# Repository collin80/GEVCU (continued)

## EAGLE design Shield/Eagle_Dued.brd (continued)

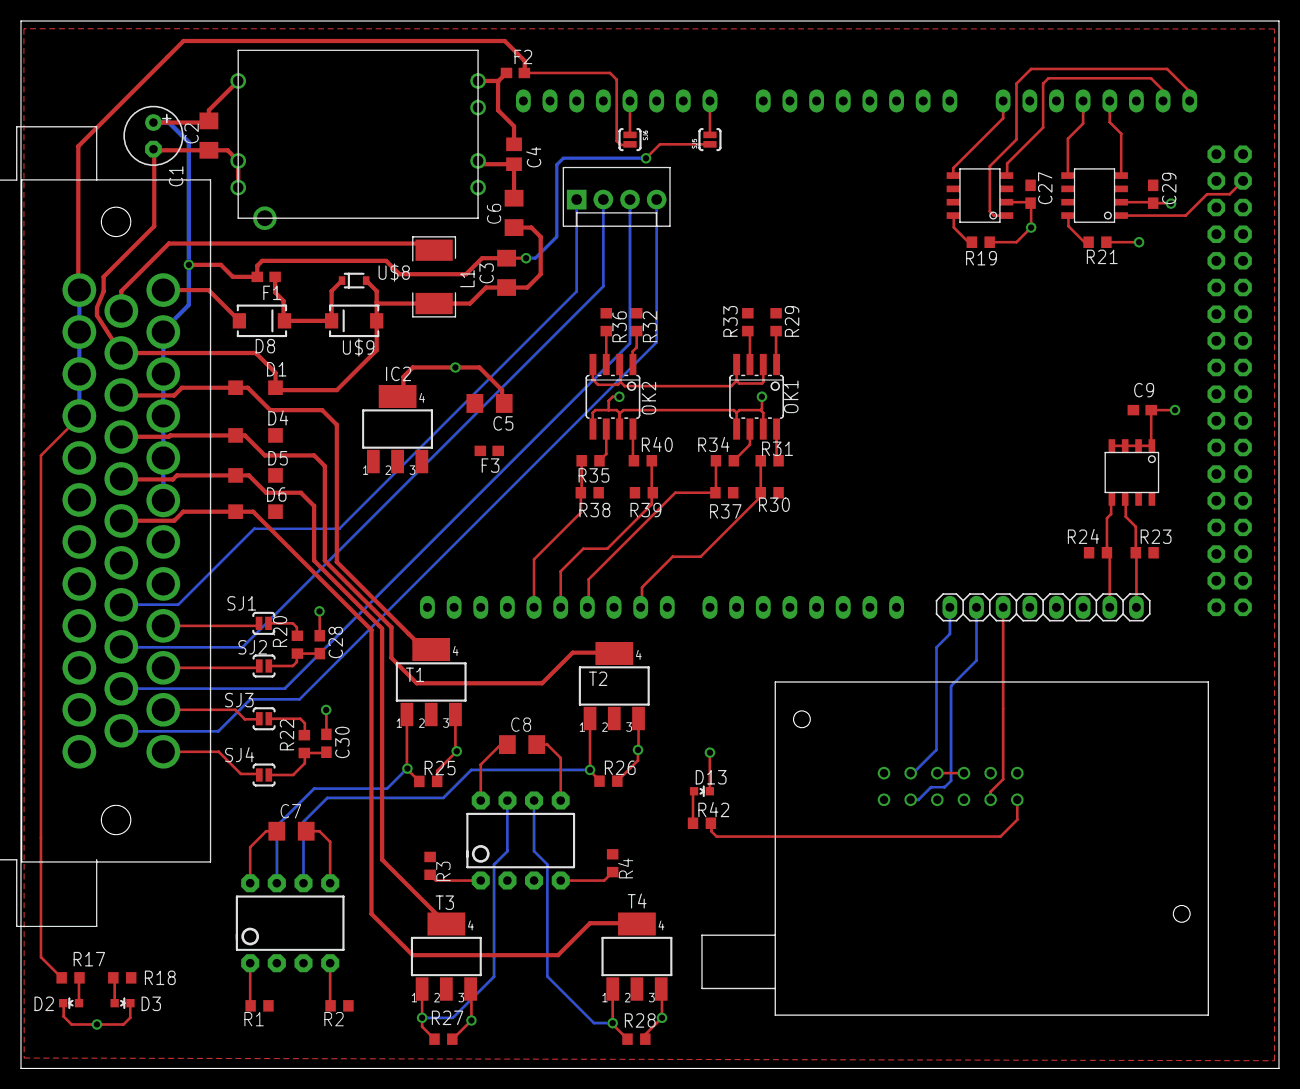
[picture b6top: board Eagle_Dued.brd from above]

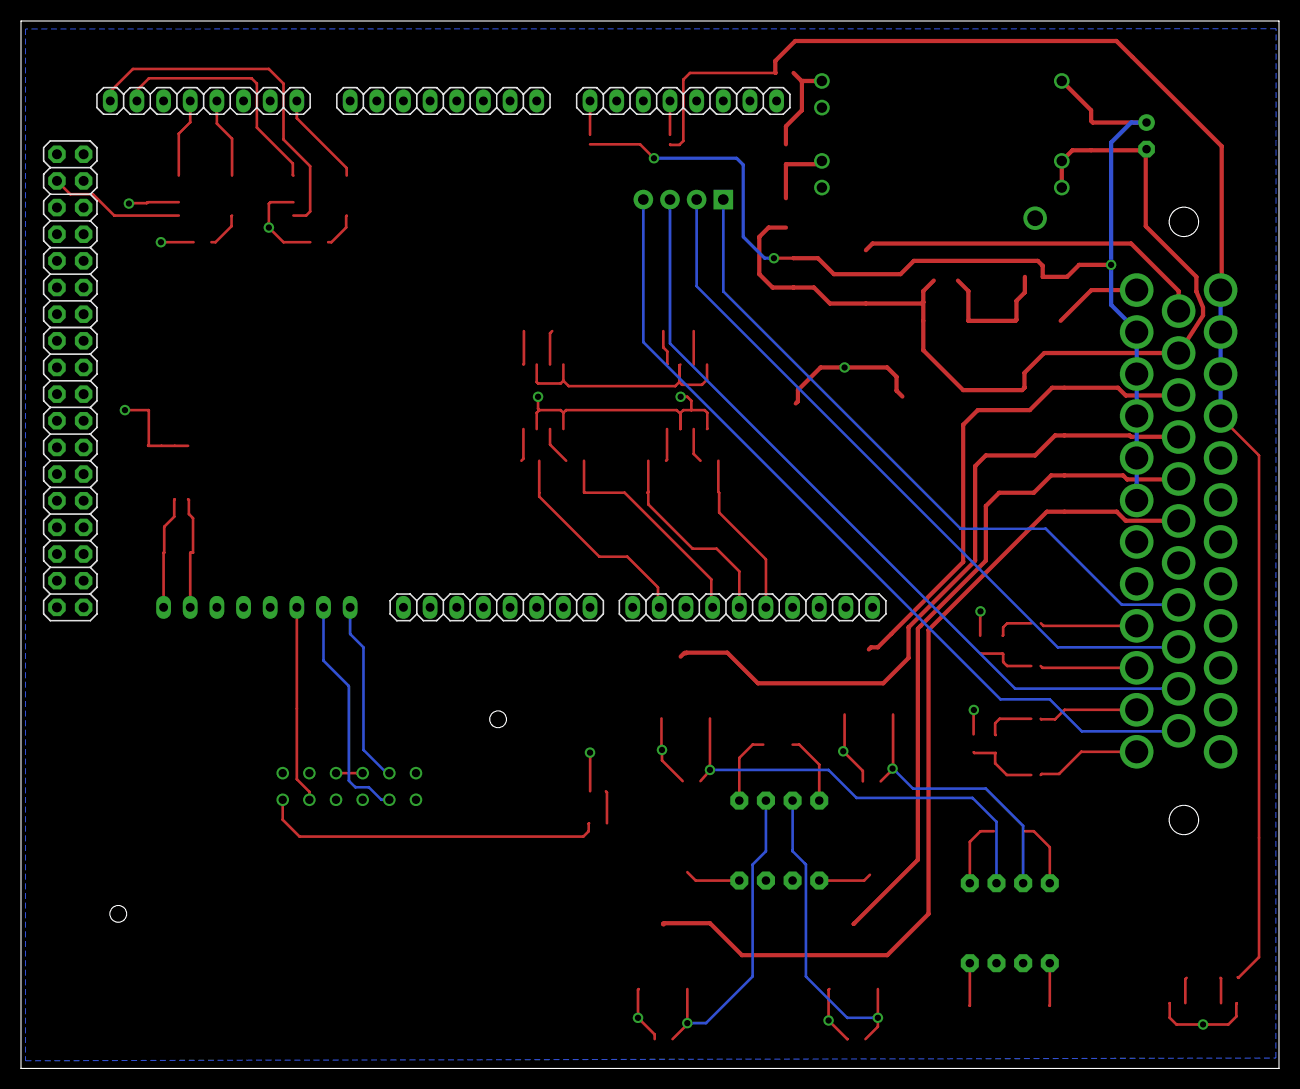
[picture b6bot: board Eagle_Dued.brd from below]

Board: 2 copper layers, 119.9 x 99.8 mm, 85 parts (6 on the bottom side), 76 nets.

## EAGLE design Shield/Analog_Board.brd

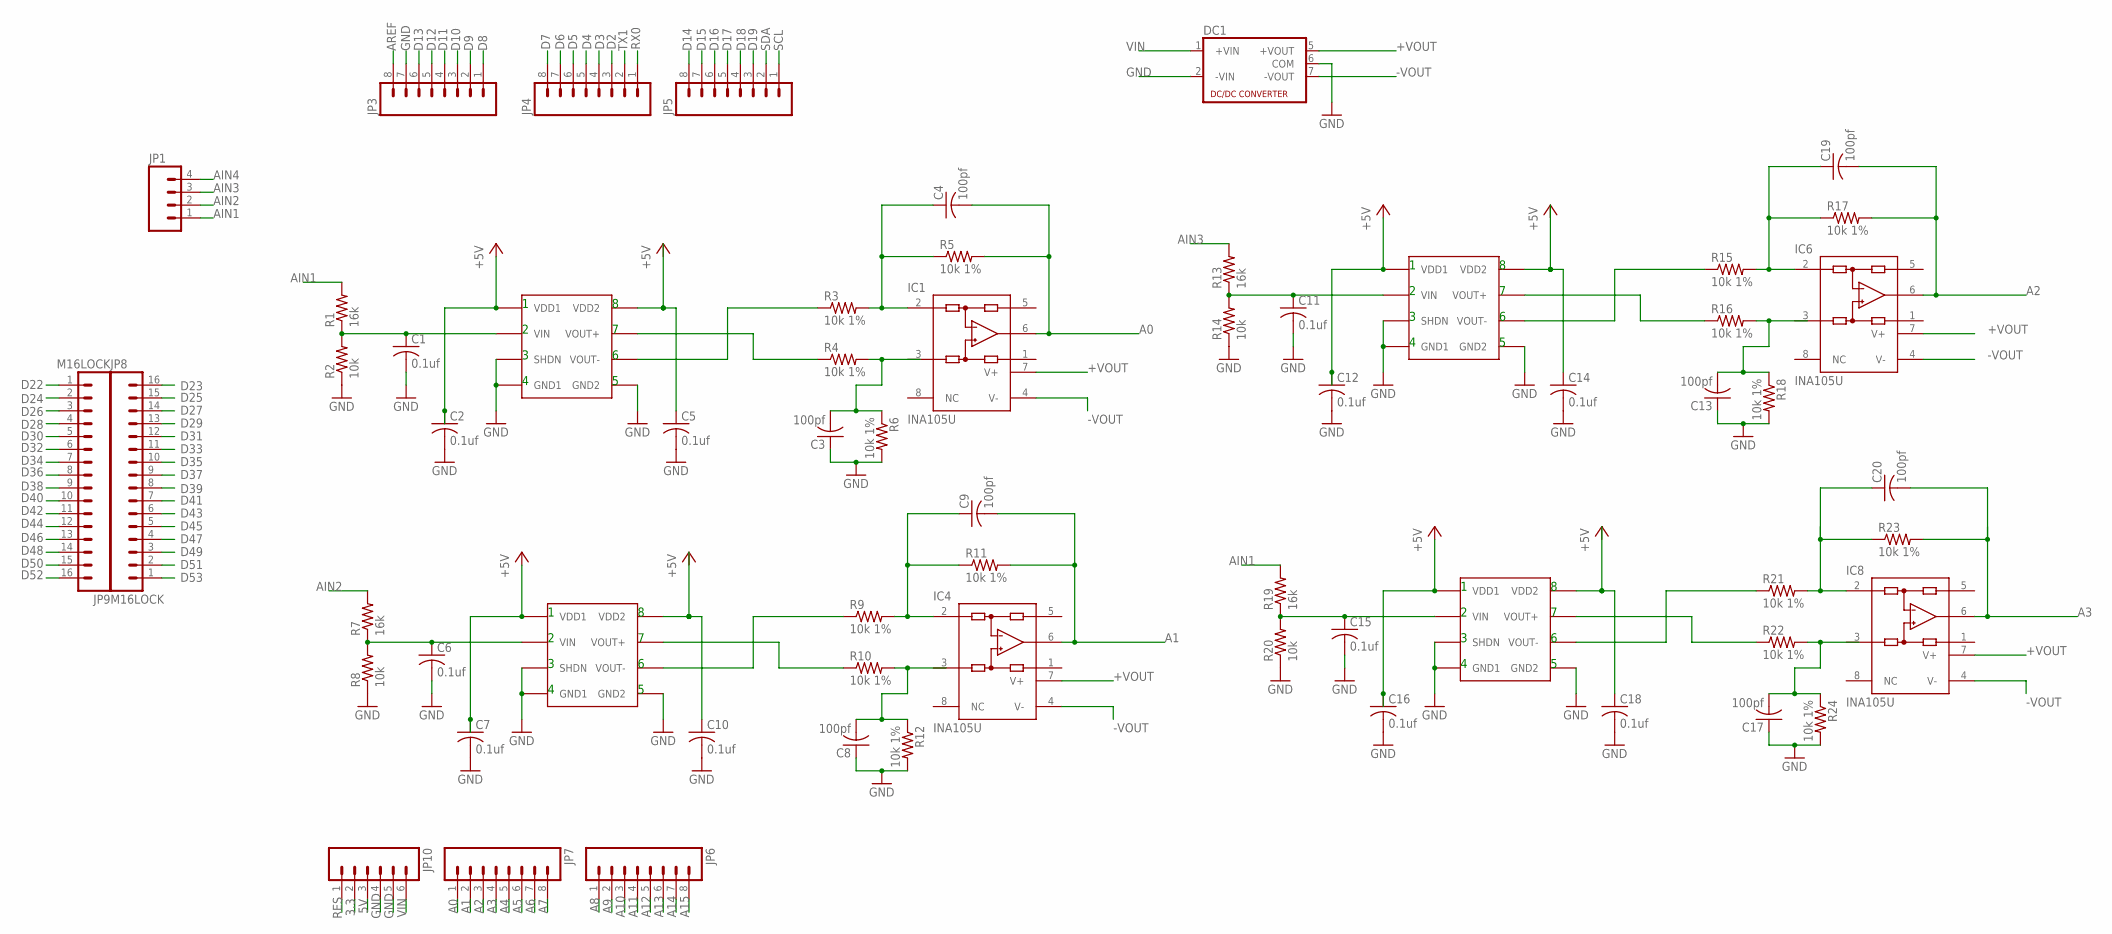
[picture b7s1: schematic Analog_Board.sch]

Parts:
C1, C2, C5, C6, C7, C10, C11, C12, C14, C15, C16, C18: 0.1uf; C0603
C3, C4, C8, C9, C13, C17, C19, C20: 100pf; C0603
DC1: NMASIP8; NMA
IC1, IC4, IC6, IC8: INA105U; SO08
IC2, IC3, IC5, IC7: ACPL-C87A-000E; SO8-WIDE
JP1: M04LOCK; 1X04_LOCK
JP3, JP4, JP5, JP6, JP7: M08LOCK; 1X08_LOCK
JP8, JP9: M16LOCK; 1X16_LOCK
JP10: M06LOCK; 1X06_LOCK
R1, R7, R13, R19: 16k; R0603
R2, R8, R14, R20: 10k; R0603
R3, R4, R5, R6, R9, R10, R11, R12, R15, R16, R17, R18, R21, R22, R23, R24: 10k 1%; R0603

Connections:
3.3: JP10.2
5V: JP10.3
+5V: C2.1, C5.1, C7.1, C10.1, C12.1, C14.1, C16.1, C18.1, IC2.1 (VDD1), IC2.8 (VDD2), IC3.1 (VDD1), IC3.8 (VDD2), IC5.1 (VDD1), IC5.8 (VDD2), IC7.1 (VDD1), IC7.8 (VDD2)
+VOUT: DC1.5 (+VOUT), IC1.7 (V+), IC4.7 (V+), IC6.7 (V+), IC8.7 (V+)
-VOUT: DC1.7 (-VOUT), IC1.4 (V-), IC4.4 (V-), IC6.4 (V-), IC8.4 (V-)
A0: C4.2, IC1.6 (OUT), JP7.1, R5.2
A1: C9.2, IC4.6 (OUT), JP7.2, R11.2
A2: C19.2, IC6.6 (OUT), JP7.3, R17.2
A3: C20.2, IC8.6 (OUT), JP7.4, R23.2
A4: JP7.5
A5: JP7.6
A6: JP7.7
A7: JP7.8
A8: JP6.1
A9: JP6.2
A10: JP6.3
A11: JP6.4
A12: JP6.5
A13: JP6.6
A14: JP6.7
A15: JP6.8
AIN2: JP1.2, R7.2
AIN3: JP1.3, R13.2
AREF: JP3.8
D2: JP4.3
D3: JP4.4
D4: JP4.5
D5: JP4.6
D6: JP4.7
D7: JP4.8
D8: JP3.1
D9: JP3.2
D10: JP3.3
D11: JP3.4
D12: JP3.5
D13: JP3.6
D14: JP5.8
D15: JP5.7
D16: JP5.6
D17: JP5.5
D18: JP5.4
D19: JP5.3
D22: JP9.1
D23: JP8.16
D24: JP9.2
D25: JP8.15
D26: JP9.3
D27: JP8.14
D28: JP9.4
D29: JP8.13
D30: JP9.5
D31: JP8.12
D32: JP9.6
D33: JP8.11
D34: JP9.7
D35: JP8.10
D36: JP9.8
D37: JP8.9
D38: JP9.9
D39: JP8.8
D40: JP9.10
D41: JP8.7
D42: JP9.11
D43: JP8.6
D44: JP9.12
D45: JP8.5
D46: JP9.13
D47: JP8.4
D48: JP9.14
D49: JP8.3
D50: JP9.15
D51: JP8.2
D52: JP9.16
D53: JP8.1
GND: C1.2, C2.2, C3.1, C5.2, C6.2, C7.2, C8.1, C10.2, C11.2, C12.2, C13.1, C14.2, C15.2, C16.2, C17.1, C18.2, DC1.2 (-VIN), DC1.6 (COM), IC2.3 (SHDN), IC2.4 (GND1), IC2.5 (GND2), IC3.3 (SHDN), IC3.4 (GND1), IC3.5 (GND2), IC5.3 (SHDN), IC5.4 (GND1), IC5.5 (GND2), IC7.3 (SHDN), IC7.4 (GND1), IC7.5 (GND2), JP3.7, JP10.4, JP10.5, R2.1, R6.2, R8.1, R12.2, R14.1, R18.2, R20.1, R24.2
unnamed: C20.1, IC8.2 (-IN), R21.2, R23.1
unnamed: IC2.7 (VOUT+), R4.1
unnamed: IC2.6 (VOUT-), R3.1
unnamed: C4.1, IC1.2 (-IN), R3.2, R5.1
unnamed: C1.1, IC2.2 (VIN), R1.1, R2.2
unnamed: C3.2, IC1.3 (+IN), R4.2, R6.1
unnamed: C6.1, IC3.2 (VIN), R7.1, R8.2
unnamed: IC3.7 (VOUT+), R10.1
unnamed: IC3.6 (VOUT-), R9.1
unnamed: C9.1, IC4.2 (-IN), R9.2, R11.1
unnamed: C8.2, IC4.3 (+IN), R10.2, R12.1
unnamed: C11.1, IC5.2 (VIN), R13.1, R14.2
unnamed: IC5.7 (VOUT+), R16.1
unnamed: IC5.6 (VOUT-), R15.1
unnamed: C19.1, IC6.2 (-IN), R15.2, R17.1
unnamed: C13.2, IC6.3 (+IN), R16.2, R18.1
unnamed: C15.1, IC7.2 (VIN), R19.1, R20.2
unnamed: IC7.7 (VOUT+), R22.1
unnamed: IC7.6 (VOUT-), R21.1
unnamed: C17.2, IC8.3 (+IN), R22.2, R24.1
RES: JP10.1
RX0: JP4.1
SCL: JP5.1
SDA: JP5.2
TX1: JP4.2
VIN: DC1.1 (+VIN), JP10.6

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
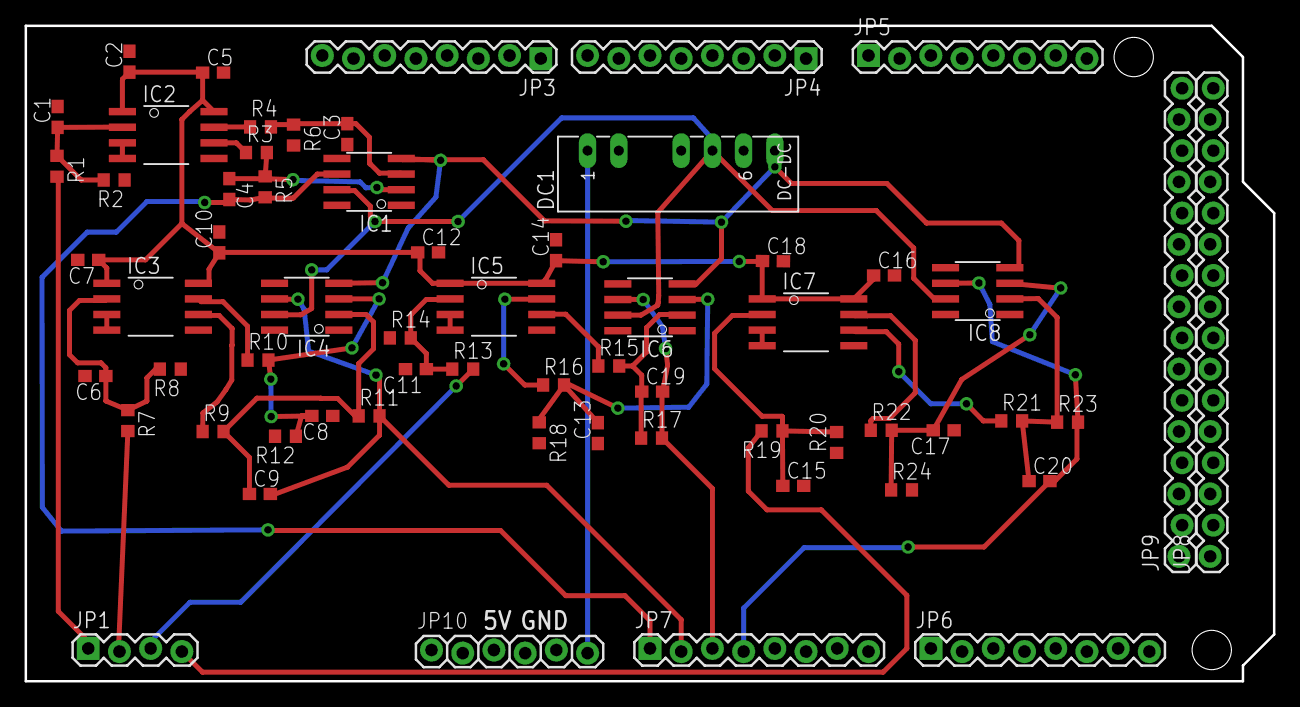
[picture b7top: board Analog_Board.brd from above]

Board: 2 copper layers, 101.6 x 53.3 mm, 62 parts (0 on the bottom side), 33 nets.

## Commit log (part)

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2014-08-21 Documentation
    Updated user manual. Added diagram for UQM Deutsche connector
2014-08-23 REVERSE and ENABLE functions
    Added annunciators for digital inputs 0-3 and the ENABLE and REVERSE
    annunciators.
2014-08-27 Added the ability to set motoring mode to either torque control or speed control. This should be exposed on the web interface as well. Also did some minor formatting.
2014-09-01 Double the ichip buffer size
2014-09-01 WiReach Setup moved to GEVCU.ino setup()
    That’s about it.
2014-09-02 Added CANCEL to loopcount
    Once Serial Console has forced ICHIP to load parameters, it sets a
    CANCEL bool to discontinue the count.
2014-09-05 Updated the readme. It was really out of date.
2014-09-07 Adjustments for Website Preload
2014-09-08 Fleshed out the FaultHandler some more. It now keeps a global log of uptime so that faults can be correlated to running time.
2014-09-16 UQM Changes and Temperature Changes
    Altered calculations for DMOC temperatures and UQM torque. Checked
    ENABLE and REVERSE inputs on UQM
2014-09-17 Changes to DMOC code to make it respect enable and reverse inputs.
2014-09-21 Postmerge
2014-09-22 Running Lights
    I’ve repurposed the RUNNING light on the STATUS panel and the running
    variable to indicate that we are receiving frames from the
    inverter/controller. If no frames are received for a certain time, the
    light goes out. If we never receive frames, it never comes on.
    In this way, we will know we are communicating or at least receiving
    traffic if we have a RUNNING advisory on the STATUS page.
2014-09-23 Tested on DMOC Bench and THING
    Reverse works. Enable works. Tested on DMOC bench and on VW Thing.
2014-09-28 Addition of the ability to set the ADC pins for pot based throttle and brake.
2014-10-02 Updated Web Site
2014-10-07 Incorporated Collin's NUKE command
2014-10-16 DC-DC COnverter Corrections
2014-10-17 Removed WIFI init
2014-12-11 Add common name to ThinkBatteryManager so it doesn't report itself as "Generic Device" any longer.
2014-12-17 Harmonize on using bool instead of boolean
    It's not good to mix bool and boolean in Arduino code for the Due. There are some subtle problems that can crop up. It's best to use the built-in C++ type "bool" when you want boolean values.
2014-12-19 Somewhat untested additions and modifications to ELM327 and OBDII stuff.
2014-12-23 Changes to make ichip code work more reliably and to aid in debugging. Also, fault handler was broken so it has been disabled for now.
2015-01-19 Add a driver class for the RX8 Dashboard. Uses the second canbus.
2015-02-25 Change BatteryManager so that it could be directly instantiated and isn't an abstract class any longer.
2015-02-25 Now using the new global objects in more places.
2015-03-01 Added a configuration object that is global and easy to use.
2015-03-06 Implementation of a new eeprom idea.
2015-03-18 move logging of 'add device' to device manager
2015-03-31 updated can matrix
2015-03-31 SystemIO sends status CAN msg and reads temperature
2015-04-09 move CanIO to separate device
2015-05-12 devices can be enabled/disabled without restart (via sendMessage()) adjust naming of output fields/variables devices can react on state change by implementing handleStateChange() devices power on the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
2015-05-12 refactor BrusaNLG5 and Charger: move general config+logic to super-class device is functional now, but NOT SAFE YET !! termination not implemented yet --> manual termination only
2015-05-14 include termination & security measures in charger, temperature derating/hysterese not implemented yet. Chargging should be quite safe now
2015-05-15 first compile, then commit...
2015-05-18 support controlling of cooling pump
2015-05-28 re-enable throttle ramping below regenMax
2015-06-09 fix conflict between eeprom and wifi, clean-up prefs handling, fix dashboard jumping needles
2015-06-12 MotorController refactoring move maxMechanicalPowerMotor, maxMechanicalPowerRegen to MotorControllerConfig as DMOC also supports it -> now configurable for DMOC handleStateChange now also passes the 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
2015-06-13 correctly handle REVERSE gear in conjunction with invertDirection
2015-06-14 fix ping assignment for GEVCU4.3 (regression from testing on v2)
2015-06-14 remove unnecessary reference to due_rtc
2015-08-13 Added CANio to canhandler
    Allow receipt of a CAN message to set digital outputs.
    Receipt of this message will trigger response of three messages to show
    state of digital outputs, analog inputs, and digital inputs.
2015-08-13 CANIO refactor
    Cleaned up CANIO a bit
2015-09-22 Initialize Wire in MemCache instead of setup()
2015-10-02 re-add PrefHandler in constructor of device subclass
    instantiate PrefHandler in constructor again as in super-class constructor getType() of sub-class can't be called
    simplify CAN data assignment in CanIO
    add analog data to CanIO messages
    move pin numbers to config.h
    add eeprom memory layout to comment of eeprom_layout.h
2015-10-14 error state was not broadcast correctly
2016-03-14 fix small bugs - if motor direction is inverted, show the value of rpm, throttle, etc. with correct sign - wifi wait longer to load params to prevent problems (no params loaded) - set hidden values f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
2016-03-25 fix typos
2016-03-26 updated website image with latest version
2016-03-28 set gauge ranges dynamically
2016-03-31 optimize WebSocket communication, recognize closure of socket by client fixed bugs
2016-04-07 fix typo
2016-04-08 remove slewType, we'll only support linear slew-rate
2016-04-17 increase update rate of ichip sockets
2016-05-24 change kwH variables to energy consumption the previous variable name was wrong and missleading also changed the calculation of used energy
2016-05-26 provide additional data from charger/dcdc to webSocktet
2016-06-04 fix wrong battery temp which caused the charger not to start fix missing 0 char at end of decoded incoming data from websocket
2016-06-06 fixed bug in slew calculation, caused jerky reduction in power correct: if(torqueTarget < torqueRequested), wrong: if(torqueTarget < 0) also apply slew for negative torque --> removed unnecessary cod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
2016-06-09 add new state "shutdown", fix WebSocket msg handling
2016-06-21 change logging so that messages can be pushed to WebSocket
2016-06-21 add warning and error sounds to dashboard
2016-06-27 add new info/warn/error sounds for notification clean-up web page
2016-06-29 clean-up a bit
2016-07-01 make start-up of charging more resilient against old error messages
2016-08-17 allow setting the energy consumption manually
2016-09-08 adjust torque/speed calculation, add support for ABS -> torque = 0
2016-09-16 print more error messages from devices to log
2016-09-17 fix wrong format descriptors in logger formatting
2016-09-22 Updated readme to cover a recent issue with this repo
2016-11-13 minor improvements
2016-11-25 keep the system running if motor controller reports error (the DCDC might still be needed), only disable the motor give the charger more time to recover from lost messages
2016-12-03 prevent continuous saving of charge state if 0 but DCDC increases it again a tiny bit
2016-12-04 optimize website
2016-12-08 fix no regen at low temperatures
2016-12-09 optimize gauge performance by using layers, prepare for multi-dial gauges
2016-12-17 finally fix start-up issues (?)
2016-12-19 config change
2016-12-26 add a 3 dial gauge for testing
2016-12-28 get gradients working for arcs
2016-12-29 more performance tweaks
2017-01-03 webservice and every dial now has its own worker (thread) which improves performance on slow multi-core systems (like the Pi or a tablet)
2017-01-04 automatically reset wifi if it does no longer respond enable/disable heater, ehps, creep, regen via websocket process heater info from GEVCUExtension
2017-01-05 first working edition of new dashboard overcame some quirks of ichip (website packager)
2017-01-08 overcome more quirks of ichip (some files can't be in sub-dir)
2017-01-10 adjust handling of heater temperature via CAN bus
2017-01-10 ensure that also 0 values are rendered
2017-02-01 fix websocket handling issues
2017-02-02 fix handling of floats reduce severity level of some log messages
2017-02-07 log incoming socket messages drop dead code
2017-03-11 prevent unnecessary writes to eeprom (prolongue live)
2017-03-11 init all values
2017-03-20 set correct pin for led on GEVCU4 board
2017-03-20 fix setting of ADC gain/offset on purged eeprom fix configuration if raw ADC should be used adjust calculation of fuel level
2017-03-23 move hardcoded values from config.h to devices align naming of defines in eeprom_layout.h move config of ADC offset/gain from eeprom to config.h
2017-03-26 make brake hold coefficient configurable find force at highest speed --> same force reuired to hold apply this force once the car stands still
2017-04-01 log ratio of motor/vehicle speed
2017-04-14 improve logging
2017-04-14 bump version
2017-05-27 add new device status indicator
2017-05-28 reduce load on tablets by not animating if delta is below a threshold and by reducing updates per second
2017-07-16 fix condition where slewPart is 0 but target and requested torque are not equal yet (e.g. 0)
2017-07-20 remove svg as ichip doesn't serve it properly
2017-10-02 correctly process missing temperature data
2017-10-03 improve annunciator, move driver info to icons
2017-10-04 do not unfold annunciator at torqueLimit due to low speed
2017-10-05 send motor speed to car bus so a filter can spoof the rpm messages
2018-08-18 add OrionBMS device, extend battery manager funcitonality
2018-09-26 another workaround for stupid ichip sending a gif image instead of an html site
2018-12-14 migrate to latest plugin version
2018-12-16 adjust websocket message handling
2018-12-17 fix sending of websocket command to ichip
2019-02-10 add CRC8 calc util (required by OrionBMS)
2019-02-12 make website minified, adjust js/css files to become minifiable
2019-02-12 initially hide icons
2019-02-12 allow to set the max input current for the charger
    fix some conversion glitches in BMS info sent via websocket
2019-02-12 current version with minified html/js/css
2019-04-08 use values for pack Volts/Amps from BMS if available, otherwise use motor controller
2019-06-30 initial draft to auto-align rpm with gear shift
2019-07-06 escape tilde sign because of ichip processing of variables
2019-07-06 Orion BMS configuration file (profile) working with GEVCU implementation
2019-07-06 add command "P" to measure the duration and voltage curve during pre-charge
2019-07-07 reduce usage of CAN mailboxes to avoid exhaustion
2019-07-07 simplify messages sent via websocket
2019-07-07 show/hide cruise control buttons when active/inactive display set rpm/kmh prevent accidental selection of text when pressing buttons/divs
2019-07-17 reduce CPU load by using prepared messages and optimizing other parts
2019-07-17 chose softer parameters for PID to avoid bucking in low torque range and have softer transitions
2019-08-05 add support to shut-down the charger add security if CAN messages from BMS are lost -> error
2019-08-05 add support for external charge current control (by solar inverter)
2019-08-06 increase power to adjust rpm
2020-04-11 bump version clean-up
2020-04-13 allow ESP32 to reload config params
2020-04-16 move carType from throttle to system drop gearChangeSupport flag, derive from input number
2020-05-19 add support for limits
2020-05-23 fix minor glitches in UI
2020-06-15 check for negative torque in the right place
2020-08-05 add log history
2020-08-09 fix logging + comments
2020-10-17 fix bug when BMS is not ready at start of charging
2020-10-23 adjust BMS settings to new code
2021-06-14 buffer outgoing serial data to prevent CAN timeouts
2022-06-27 PDF Document Added
